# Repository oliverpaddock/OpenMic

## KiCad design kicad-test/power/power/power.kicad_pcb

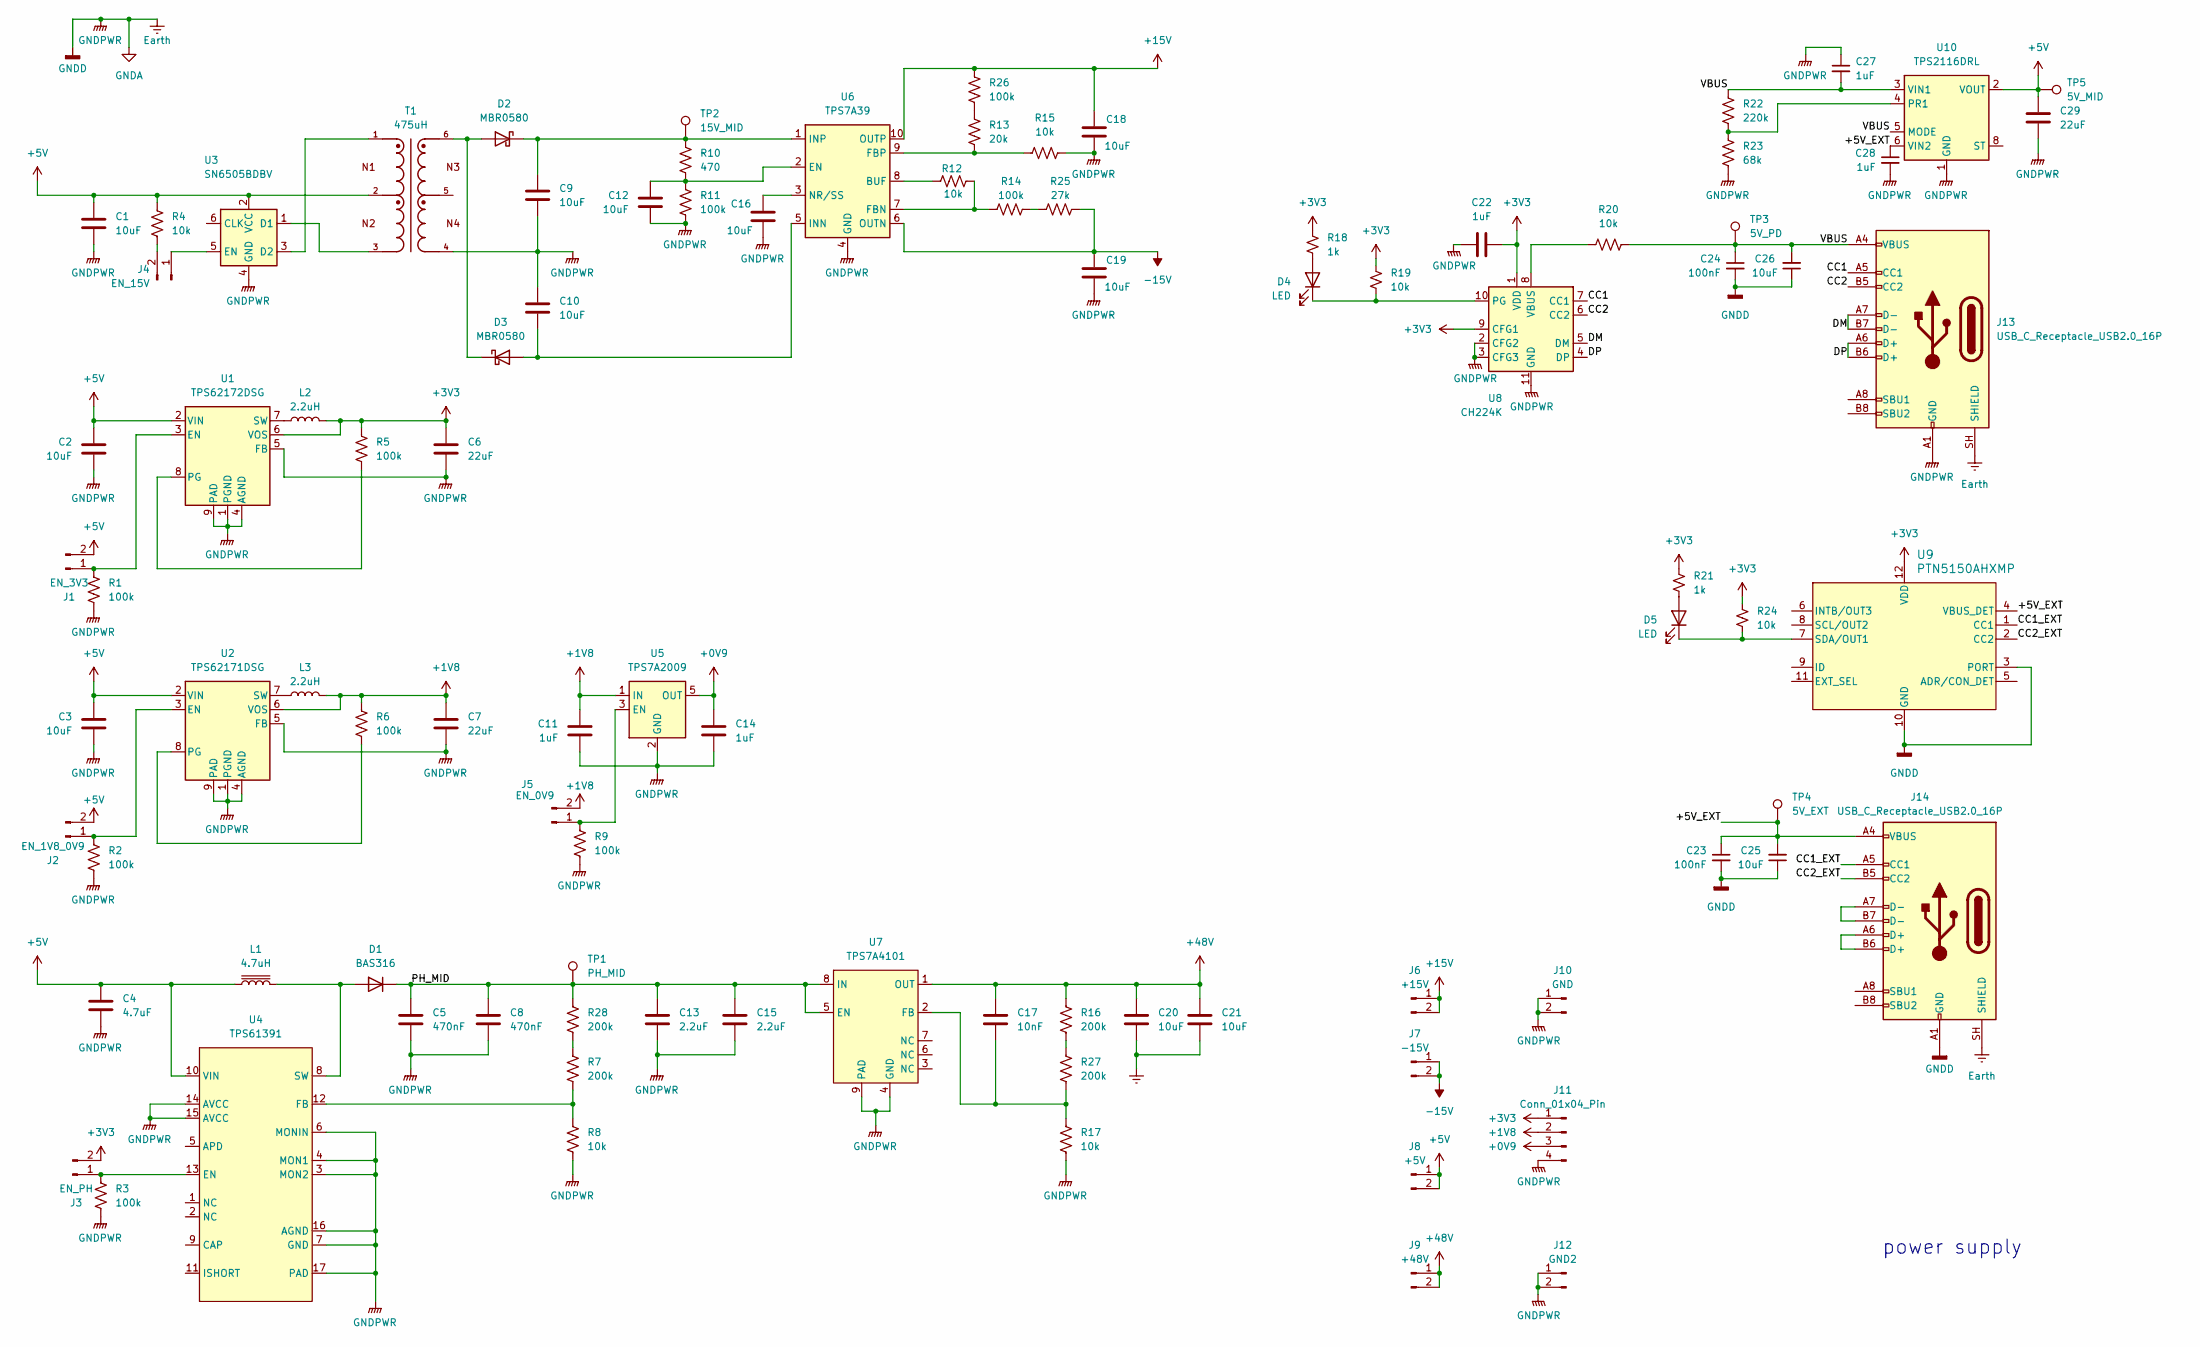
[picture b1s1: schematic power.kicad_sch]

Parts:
C1, C2, C3, C9, C10, C12, C16, C18, C19, C25, C26: 10uF; C_0805_2012Metric_Pad1.18x1.45mm_HandSolder; MPN CL21A106KAYNNNE; LCSC C15850
C4: 4.7uF; C_0805_2012Metric_Pad1.18x1.45mm_HandSolder; MPN CL21A475KAQNNNE; LCSC C1779
C5, C8: 470nF; C_0805_2012Metric_Pad1.18x1.45mm_HandSolder; MPN CL21B474KBFNNNE; LCSC C13967
C6, C7, C29: 22uF; C_0805_2012Metric_Pad1.18x1.45mm_HandSolder; MPN CL21A226MAQNNNE; LCSC C45783
C11, C14, C22, C27, C28: 1uF; C_0805_2012Metric_Pad1.18x1.45mm_HandSolder; MPN CL21B105KBFNNNE; LCSC C28323
C13, C15: 2.2uF; C_0805_2012Metric_Pad1.18x1.45mm_HandSolder; MPN CL21A225KBQNNNE; LCSC C377773
C17: 10nF; C_0805_2012Metric_Pad1.18x1.45mm_HandSolder; MPN CL21B103KBANNNC; LCSC C1710
C20, C21: 10uF; C_1210_3225Metric_Pad1.33x2.70mm_HandSolder; MPN CL21A106KAYNNNE; LCSC C15850
C23, C24: 100nF; C_0805_2012Metric_Pad1.18x1.45mm_HandSolder; MPN CC0805KRX7R9BB104; LCSC C49678
D1: BAS316; D_SOD-323; MPN BAS316; LCSC C8488
D2, D3: MBR0580; D_SOD-123; MPN MBR0580; LCSC C77339
D4, D5: LED; LED_0805_2012Metric_Pad1.15x1.40mm_HandSolder; MPN NCD0805R1; LCSC C84256
J1: EN_3V3; PinHeader_1x02_P2.54mm_Vertical
J2: EN_1V8_0V9; PinHeader_1x02_P2.54mm_Vertical
J3: EN_PH; PinHeader_1x02_P2.54mm_Vertical
J4: EN_15V; PinHeader_1x02_P2.54mm_Vertical
J5: EN_0V9; PinHeader_1x02_P2.54mm_Vertical
J6: +15V; PinHeader_1x02_P2.54mm_Vertical
J7: -15V; PinHeader_1x02_P2.54mm_Vertical
J8: +5V; PinHeader_1x02_P2.54mm_Vertical
J9: +48V; PinHeader_1x02_P2.54mm_Vertical
J10: GND; PinHeader_1x02_P2.54mm_Vertical
J11: Conn_01x04_Pin; PinHeader_1x04_P2.54mm_Vertical
J12: GND2; PinHeader_1x02_P2.54mm_Vertical
J13, J14: USB_C_Receptacle_USB2.0_16P; USB_C_Receptacle_HRO_TYPE-C-31-M-12; MPN TYPE-C-31-M-12; LCSC C165948
L1: 4.7uH; L_Wuerth_PMCI-201610; MPN DFE201612E-4R7M=P2; LCSC C3223763
L2, L3: 2.2uH; L_Wurth_WE-LQSH-3012; MPN ANR3015T2R2M; LCSC C6364793
R1, R2, R3, R5, R6, R9, R11, R14, R26: 100k; R_0805_2012Metric_Pad1.20x1.40mm_HandSolder; MPN 0805W8F1003T5E; LCSC C149504
R4, R8, R12, R15, R17, R19, R20, R24: 10k; R_0805_2012Metric_Pad1.20x1.40mm_HandSolder; MPN 0805W8F1002T5E; LCSC C17414
R7, R16, R27, R28: 200k; R_0805_2012Metric_Pad1.20x1.40mm_HandSolder; MPN 0805W8F2003T5E; LCSC C17539
R10: 470; R_0805_2012Metric_Pad1.20x1.40mm_HandSolder; MPN 0805W8F4700T5E; LCSC C17710
R13: 20k; R_0805_2012Metric_Pad1.20x1.40mm_HandSolder; MPN 0805W8F2002T5E; LCSC C4328
R18, R21: 1k; R_0805_2012Metric_Pad1.20x1.40mm_HandSolder; MPN 0805W8F1001T5E; LCSC C17513
R22: 220k; R_0805_2012Metric_Pad1.20x1.40mm_HandSolder; MPN 0805W8F2203T5E; LCSC C17556
R23: 68k; R_0805_2012Metric_Pad1.20x1.40mm_HandSolder; MPN 0805W8F6802T5E; LCSC C17801
R25: 27k; R_0805_2012Metric_Pad1.20x1.40mm_HandSolder; MPN 0805W8F2702T5E; LCSC C17593
T1: 475uH; Wurth Elektronik 760390015; MPN 760390015; LCSC C249186
TP1: PH_MID; TestPoint_Keystone_5010-5014_Multipurpose
TP2: 15V_MID; TestPoint_Keystone_5010-5014_Multipurpose
TP3: 5V_PD; TestPoint_Keystone_5010-5014_Multipurpose
TP4: 5V_EXT; TestPoint_Keystone_5010-5014_Multipurpose
TP5: 5V_MID; TestPoint_Keystone_5010-5014_Multipurpose
U1: TPS62172DSG; WSON-8-1EP_2x2mm_P0.5mm_EP0.9x1.6mm_ThermalVias; MPN TPS62172DSGR; LCSC C59873
U2: TPS62171DSG; WSON-8-1EP_2x2mm_P0.5mm_EP0.9x1.6mm_ThermalVias; MPN TPS62171DSGR; LCSC C2071102
U3: SN6505BDBV; SOT-23-6; MPN SN6505BDBVR; LCSC C74518
U4: TPS61391; WQFN-16-1EP_3x3mm_P0.5mm_EP1.6x1.6mm; MPN TPS61391RTER; LCSC C1852151
U5: TPS7A2009; SOT-23-5; MPN TPS7A2009PDBVR; LCSC C2861215
U6: TPS7A39; Texas_S-PVSON-N10_ThermalVias; MPN TPS7A3901DSCR; LCSC C2685819
U7: TPS7A4101; Texas_DGN0008B_VSSOP-8-1EP_3x3mm_P0.65mm_EP2x3mm_Mask1.88x1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; MPN TPS7A4101DGNR; LCSC C111739
U8: CH224K; SSOP-10-1EP_3.9x4.9mm_P1mm_EP2.1x3.3mm; MPN CH224K; LCSC C970725
U9: PTN5150AHXMP; Texas_X2QFN-12_1.6x1.6mm_P0.4mm; MPN PTN5150AHXMP; LCSC C2651889
U10: TPS2116DRL; SOT-583-8; MPN TPS2116DRLR; LCSC C3235557

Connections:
+0V9: C14.1, J11.3, U5.5 (OUT)
+1V8: C7.1, C11.1, J5.2, J11.2, L3.2, R6.1, U2.6 (VOS), U5.1 (IN)
+3V3: C6.1, C22.1, J3.2, J11.1, L2.2, R5.1, R18.1, R19.1, R21.1, R24.1, U1.6 (VOS), U8.1 (VDD), U8.9 (CFG1), U9.12 (VDD)
+5V: C1.1, C2.1, C3.1, C4.1, C29.1, J1.2, J2.2, J8.1, J8.2, L1.1, R4.2, T1.2, TP5.1 (1_1), U1.2 (VIN), U2.2 (VIN), U3.2 (VCC), U4.10 (VIN), U10.2 (VOUT), U10.7 (VOUT)
+15V: C18.1, J6.1, J6.2, R26.1, U6.10 (OUTP)
+48V: C17.1, C20.1, C21.1, J9.1, J9.2, R16.1, U7.1 (OUT)
-15V: C19.1, J7.1, J7.2, R25.2, U6.6 (OUTN)
/+5V_EXT: C23.1, C25.2, C28.1, J14.A4 (VBUS), J14.A9 (VBUS), J14.B4 (VBUS), J14.B9 (VBUS), TP4.1 (1_1), U9.4 (VBUS_DET), U10.6 (VIN2)
/CC1: J13.A5 (CC1), U8.7 (CC1)
/CC1_EXT: J14.A5 (CC1), U9.1 (CC1)
/CC2: J13.B5 (CC2), U8.6 (CC2)
/CC2_EXT: J14.B5 (CC2), U9.2 (CC2)
/DM: J13.A7 (D-), J13.B7 (D-), U8.5 (DM)
/DP: J13.A6 (D+), J13.B6 (D+), U8.4 (DP)
/PH_MID: C5.1, C8.1, C13.1, C15.1, D1.1 (K), R28.1, TP1.1 (1_1), U7.5 (EN), U7.8 (IN)
/VBUS: C24.1, C26.2, C27.2, J13.A4 (VBUS), J13.A9 (VBUS), J13.B4 (VBUS), J13.B9 (VBUS), R20.2, R22.1, TP3.1 (1_1), U10.3 (VIN1), U10.5 (MODE)
Earth: C1.2, C2.2, C3.2, C4.2, C5.2, C6.2, C7.2, C8.2, C9.2, C10.1, C11.2, C12.2, C13.2, C14.2, C15.2, C16.2, C18.2, C19.2, C20.2, C21.2, C22.2, C23.2, C24.2, C25.1, C26.1, C27.1, C28.2, C29.2, J10.1, J10.2, J11.4, J12.1, J12.2, J13.A1 (GND), J13.A12 (GND), J13.B1 (GND), J13.B12 (GND), J13.SH (SHIELD), J14.A1 (GND), J14.A12 (GND), J14.B1 (GND), J14.B12 (GND), J14.SH (SHIELD), R1.2, R2.2, R3.2, R8.2, R9.2, R11.2, R15.2, R17.2, R23.2, T1.4, U1.1 (PGND), U1.4 (AGND), U1.5 (FB), U1.9 (PAD), U2.1 (PGND), U2.4 (AGND), U2.5 (FB), U2.9 (PAD), U3.4 (GND), U4.3 (MON2), U4.4 (MON1), U4.6 (MONIN), U4.7 (GND), U4.14 (AVCC), U4.15 (AVCC), U4.16 (AGND), U4.17 (PAD), U5.2 (GND), U6.4 (GND), U6.11 (GND), U7.4 (GND), U7.9 (PAD), U8.2 (CFG2), U8.3 (CFG3), U8.11 (GND), U9.3 (PORT), U9.10 (GND), U10.1 (GND)
unnamed: D1.2 (A), L1.2, U4.8 (SW)
unnamed: D2.2 (A), D3.1 (K), T1.6
unnamed: C9.1, D2.1 (K), R10.1, TP2.1 (1_1), U6.1 (INP)
unnamed: C10.2, D3.2 (A), U6.5 (INN)
unnamed: D4.2 (A), R18.2
unnamed: D4.1 (K), R19.2, U8.10 (PG)
unnamed: D5.2 (A), R21.2
unnamed: D5.1 (K), R24.2, U9.7 (SDA/OUT1)
unnamed: J1.1, R1.1, U1.3 (EN)
unnamed: J2.1, R2.1, U2.3 (EN)
unnamed: J3.1, R3.1, U4.13 (EN)
unnamed: J4.1, U3.5 (EN)
unnamed: J4.2, R4.1
unnamed: J5.1, R9.1, U5.3 (EN)
unnamed: J14.A6 (D+), J14.B6 (D+)
unnamed: J14.A7 (D-), J14.B7 (D-)
unnamed: R13.1, R26.2
unnamed: R14.2, R25.1
unnamed: R16.2, R27.1
unnamed: R7.1, R28.2
unnamed: R5.2, U1.8 (PG)
unnamed: L2.1, U1.7 (SW)
unnamed: R6.2, U2.8 (PG)
unnamed: L3.1, U2.7 (SW)
unnamed: T1.3, U3.1 (D1)
unnamed: T1.1, U3.3 (D2)
unnamed: R7.2, R8.1, U4.12 (FB)
unnamed: R12.1, U6.8 (BUF)
unnamed: C12.1, R10.2, R11.1, U6.2 (EN)
unnamed: R12.2, R14.1, U6.7 (FBN)
unnamed: R13.2, R15.1, U6.9 (FBP)
unnamed: C16.1, U6.3 (NR/SS)
unnamed: C17.2, R17.1, R27.2, U7.2 (FB)
unnamed: R20.1, U8.8 (VBUS)
unnamed: R22.2, R23.1, U10.4 (PR1)

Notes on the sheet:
power supply

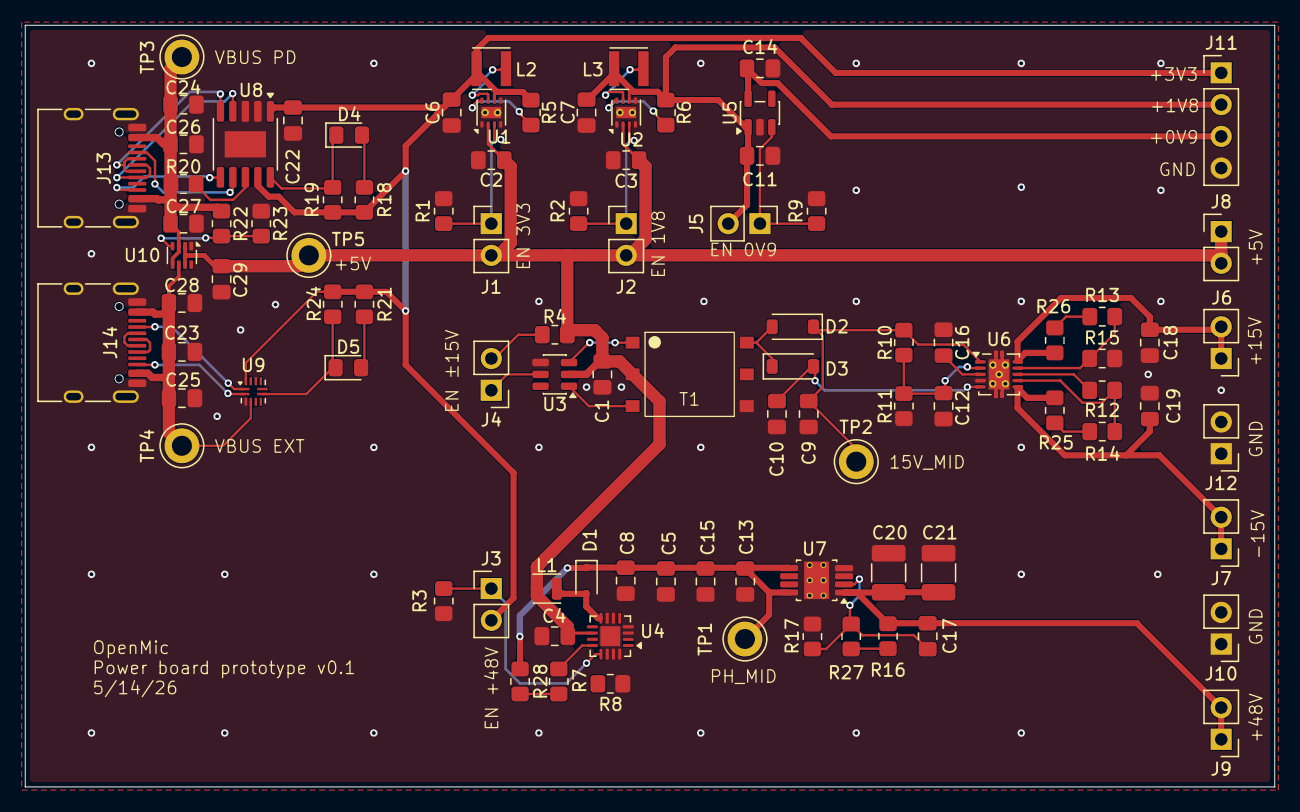
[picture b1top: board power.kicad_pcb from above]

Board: 2 copper layers, 100.0 x 61.0 mm, 95 parts (0 on the bottom side), 52 nets.

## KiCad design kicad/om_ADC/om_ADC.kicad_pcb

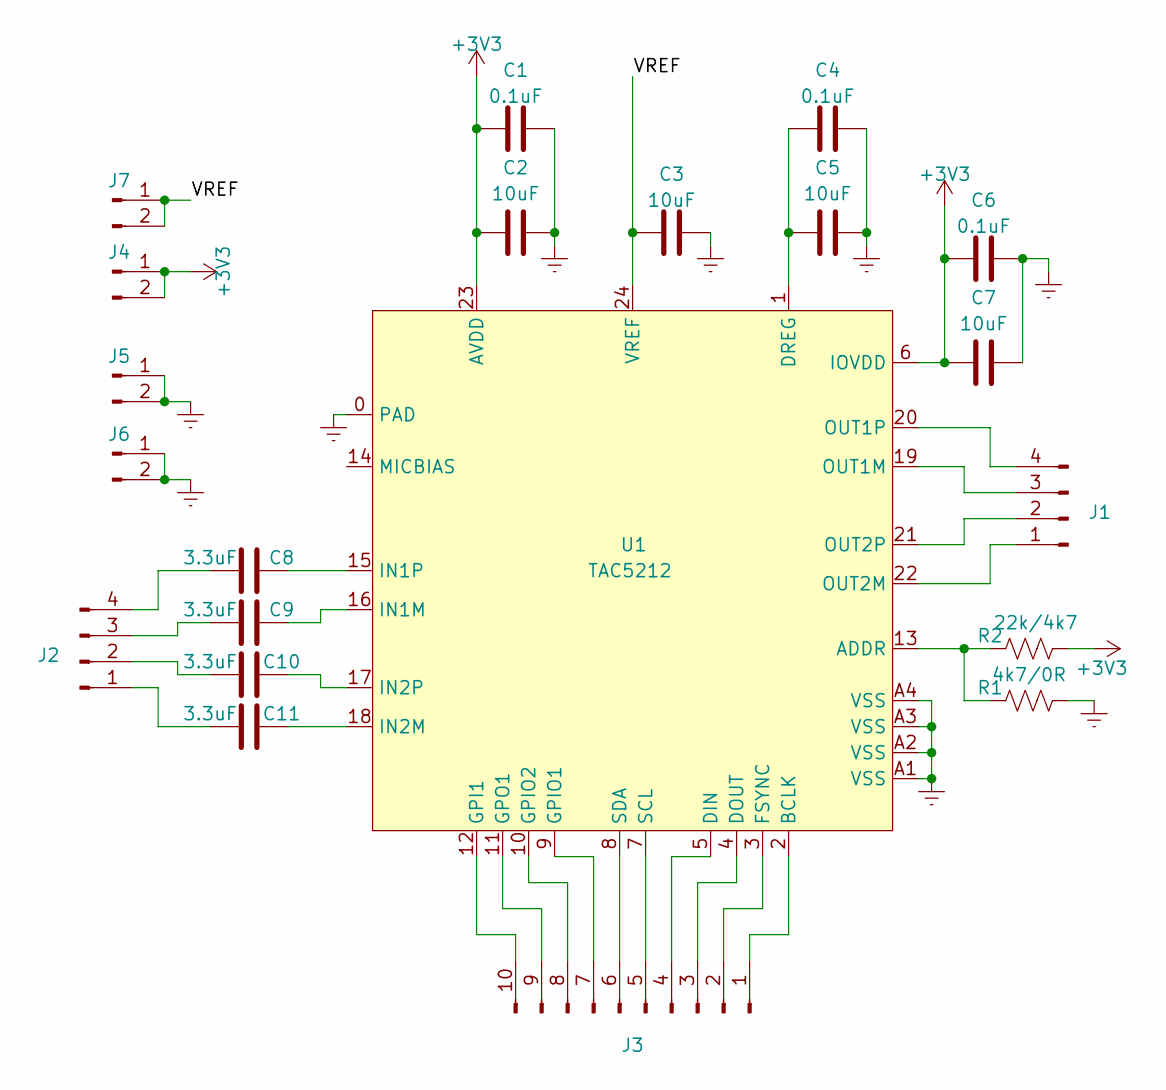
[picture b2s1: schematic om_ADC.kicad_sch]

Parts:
C1, C4, C6: 0.1uF; C_0603_1608Metric_Pad1.08x0.95mm_HandSolder
C2, C3, C5, C7: 10uF; C_0603_1608Metric_Pad1.08x0.95mm_HandSolder
C8, C9, C10, C11: 3.3uF; C_0603_1608Metric_Pad1.08x0.95mm_HandSolder
J1, J2: Conn_01x04_Pin; PinHeader_1x04_P2.54mm_Vertical
J3: Conn_01x10_Pin; PinHeader_1x10_P2.54mm_Vertical
J4, J5, J6, J7: Conn_01x02_Pin; PinHeader_1x02_P2.54mm_Vertical
R1: 4k7/0R; R_0603_1608Metric_Pad0.98x0.95mm_HandSolder
R2: 22k/4k7; R_0603_1608Metric_Pad0.98x0.95mm_HandSolder
U1: TAC5212

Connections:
+3V3: C1.1, C2.1, C6.1, C7.1, J4.1, J4.2, R2.2, U1.6 (IOVDD), U1.23 (AVDD)
/VREF: C3.1, J7.1, J7.2, U1.24 (VREF)
Earth: C1.2, C2.2, C3.2, C4.2, C5.2, C6.2, C7.2, J5.1, J5.2, J6.1, J6.2, R1.2, U1.0 (PAD), U1.A1 (VSS), U1.A2 (VSS), U1.A3 (VSS), U1.A4 (VSS)
unnamed: J1.1, U1.22 (OUT2M)
unnamed: J1.2, U1.21 (OUT2P)
unnamed: J1.3, U1.19 (OUT1M)
unnamed: J1.4, U1.20 (OUT1P)
unnamed: C11.1, J2.1
unnamed: C10.1, J2.2
unnamed: C9.1, J2.3
unnamed: C8.1, J2.4
unnamed: J3.1, U1.2 (BCLK)
unnamed: J3.2, U1.3 (FSYNC)
unnamed: J3.3, U1.4 (DOUT)
unnamed: J3.4, U1.5 (DIN)
unnamed: J3.5, U1.7 (SCL)
unnamed: J3.6, U1.8 (SDA)
unnamed: J3.7, U1.9 (GPIO1)
unnamed: J3.8, U1.10 (GPIO2)
unnamed: J3.9, U1.11 (GPO1)
unnamed: J3.10, U1.12 (GPI1)
unnamed: R1.1, R2.1, U1.13 (ADDR)
unnamed: C4.1, C5.1, U1.1 (DREG)
unnamed: C9.2, U1.16 (IN1M)
unnamed: C8.2, U1.15 (IN1P)
unnamed: C11.2, U1.18 (IN2M)
unnamed: C10.2, U1.17 (IN2P)

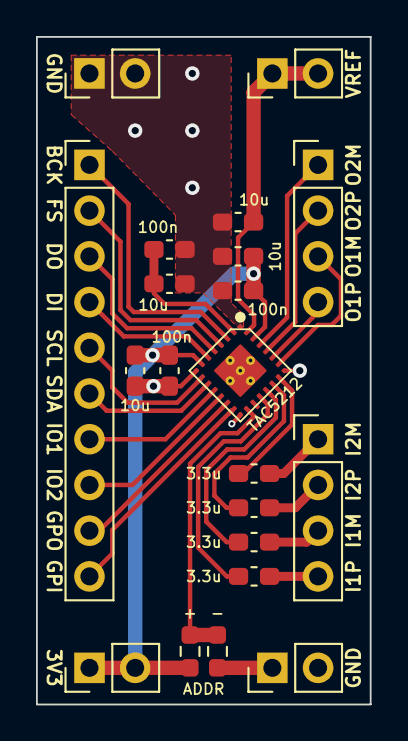
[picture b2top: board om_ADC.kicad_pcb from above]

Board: 2 copper layers, 18.5 x 37.1 mm, 21 parts (0 on the bottom side), 27 nets.

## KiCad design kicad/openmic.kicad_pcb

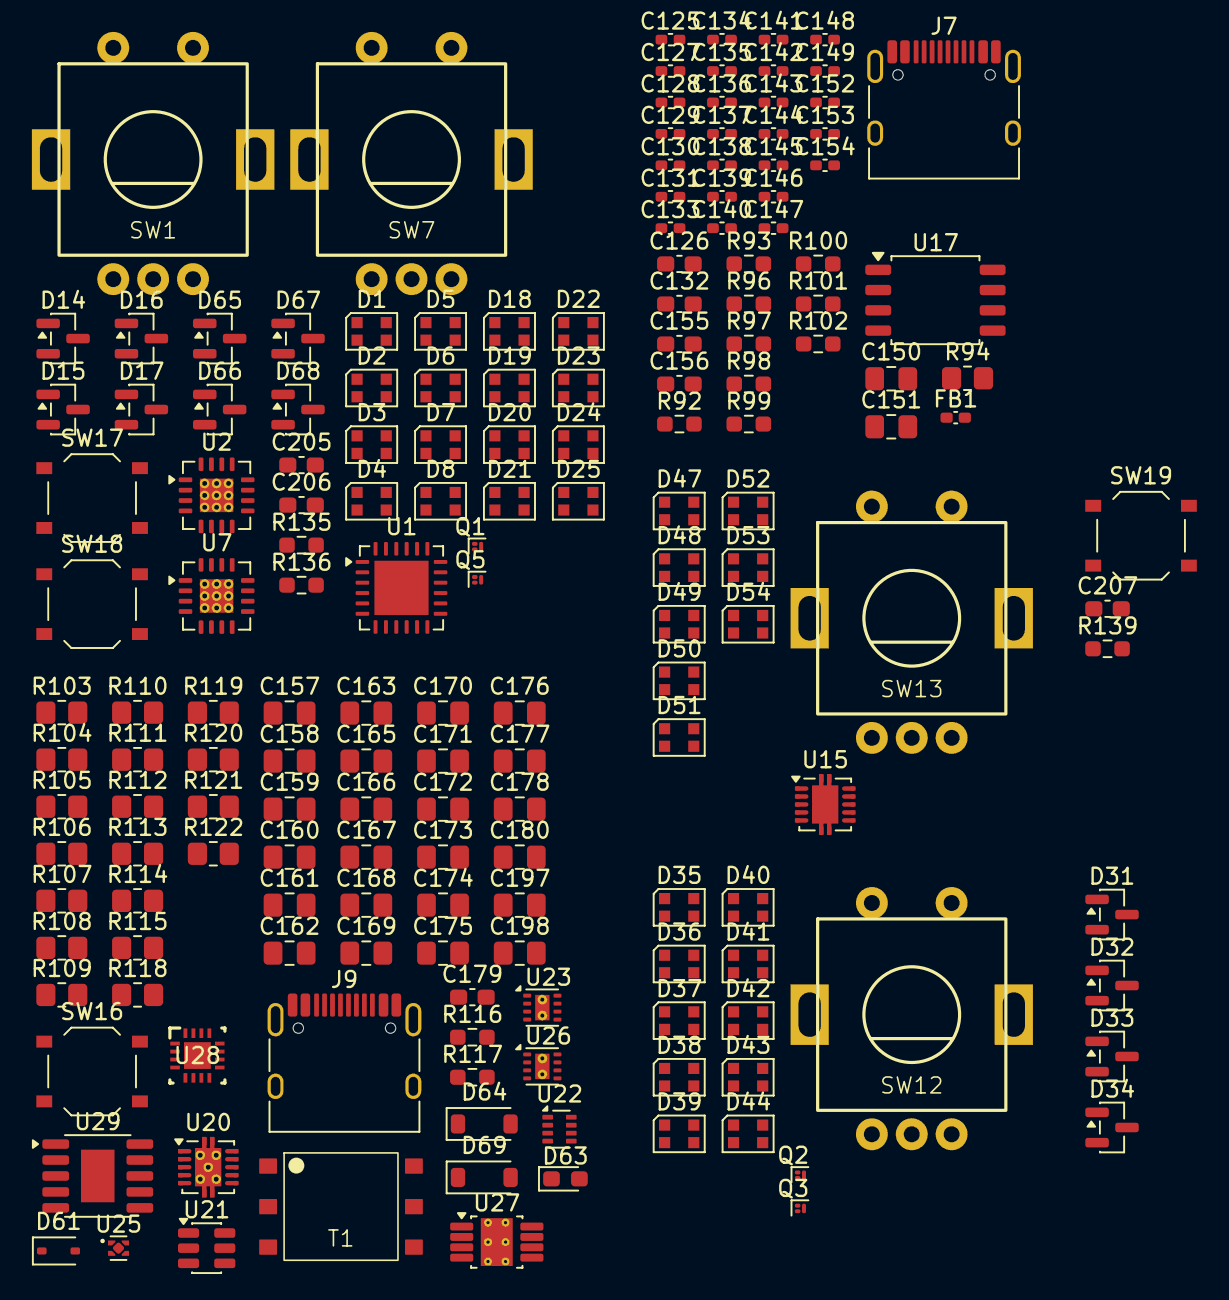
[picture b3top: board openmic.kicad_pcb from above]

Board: 2 copper layers, 173 parts (0 on the bottom side), 98 nets, no tracks yet.

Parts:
C125, C127, C128, C129, C130, C131, C133, C134, C135, C136, C137, C138, C139, C140, C141, C142, C143, C144, C145, C146, C147, C148, C149, C153, C154: 100nF; C_0402_1005Metric_Pad0.74x0.62mm_HandSolder
C126, C132, C179, C205, C206, C207: 100nF; C_0603_1608Metric_Pad1.08x0.95mm_HandSolder
C150, C197: 100nF; C_0805_2012Metric_Pad1.18x1.45mm_HandSolder
C151, C157, C158, C159, C160, C161, C162, C165, C167, C177, C178, C198: 10uF; C_0805_2012Metric_Pad1.18x1.45mm_HandSolder
C152: 1uF; C_0402_1005Metric_Pad0.74x0.62mm_HandSolder
C155, C156: 22pF; C_0603_1608Metric_Pad1.08x0.95mm_HandSolder
C163, C166, C168: 22uF; C_0805_2012Metric_Pad1.18x1.45mm_HandSolder
C169, C170, C180: 1uF; C_0805_2012Metric_Pad1.18x1.45mm_HandSolder
C171: 4.7uF; C_0805_2012Metric_Pad1.18x1.45mm_HandSolder
C172, C173: 470nF; C_0805_2012Metric_Pad1.18x1.45mm_HandSolder
C174, C175: 2.2uF; C_0805_2012Metric_Pad1.18x1.45mm_HandSolder
C176: 10nF; C_0805_2012Metric_Pad1.18x1.45mm_HandSolder
D1, D2, D3, D4, D5, D6, D7, D8, D18, D19, D20, D21, D22, D23, D24, D25, D35, D36, D37, D38, D39, D40, D41, D42, D43, D44, D47, D48, D49, D50, D51, D52, D53, D54: WS2812B-2020; LED_WS2812B-2020_PLCC4_2.0x2.0mm
D14, D15, D16, D17, D65, D66, D67, D68: BAV99; SOT-23
D31, D32, D33, D34: BAT54S; SOT-23
D61: BAS316; D_SOD-323
D63: LED; LED_0603_1608Metric_Pad1.05x0.95mm_HandSolder
D64, D69: MBR0580; D_SOD-123
FB1: 600R; L_0402_1005Metric_Pad0.77x0.64mm_HandSolder
J7, J9: USB_C_Receptacle_USB2.0_16P; USB_C_Receptacle_HRO_TYPE-C-31-M-12
Q1, Q2, Q3, Q5: CSD13380F3; Texas_PicoStar_DFN-3_0.69x0.60mm
R92, R96, R98, R99, R100, R116, R135, R136, R139: 47k; R_0603_1608Metric_Pad0.98x0.95mm_HandSolder
R93: 220k; R_0603_1608Metric_Pad0.98x0.95mm_HandSolder
R94, R104, R106, R108, R113, R120, R122: 10k; R_0805_2012Metric_Pad1.20x1.40mm_HandSolder
R97: 100k; R_0603_1608Metric_Pad0.98x0.95mm_HandSolder
R101: 1M; R_0603_1608Metric_Pad0.98x0.95mm_HandSolder
R102: 30; R_0603_1608Metric_Pad0.98x0.95mm_HandSolder
R103: 118k; R_0805_2012Metric_Pad1.20x1.40mm_HandSolder
R105: 499k; R_0805_2012Metric_Pad1.20x1.40mm_HandSolder
R107, R111, R112, R114: 100k; R_0805_2012Metric_Pad1.20x1.40mm_HandSolder
R109: 127k; R_0805_2012Metric_Pad1.20x1.40mm_HandSolder
R110: 330k; R_0805_2012Metric_Pad1.20x1.40mm_HandSolder
R115: 475k; R_0805_2012Metric_Pad1.20x1.40mm_HandSolder
R117: 1k; R_0603_1608Metric_Pad0.98x0.95mm_HandSolder
R118: 392k; R_0805_2012Metric_Pad1.20x1.40mm_HandSolder
R119: 12k; R_0805_2012Metric_Pad1.20x1.40mm_HandSolder
R121: 1k; R_0805_2012Metric_Pad1.20x1.40mm_HandSolder
SW1, SW7, SW12, SW13: RotaryEncoder; PEC11L
SW16, SW17, SW18, SW19: SW_Push; SW_Push_1P1T_XKB_TS-1187A
T1: 475uH; Wurth Elektronik 760390015
U1: THAT5263; QFN-24-1EP_5x5mm_P0.65mm_EP3.4x3.4mm
U2, U7: THAT1580; QFN-16-1EP_4x4mm_P0.65mm_EP2.1x2.1mm_ThermalVias
U15: OPA1622; Texas_S-PVSON-N10
U17: W25Q32JVSS; SOIC-8_5.3x5.3mm_P1.27mm
U20: TPS7A39; Texas_S-PVSON-N10_ThermalVias
U21: SN6505BDBV; SOT-23-6
U22: TPS2116DRL; SOT-583-8
U23: TPS62172DSG; WSON-8-1EP_2x2mm_P0.5mm_EP0.9x1.6mm_ThermalVias
U25: TPS7A2009; Texas_X2SON-4_1x1mm_P0.65mm
U26: TPS62171DSG; WSON-8-1EP_2x2mm_P0.5mm_EP0.9x1.6mm_ThermalVias
U27: TPS7A4101; Texas_DGN0008B_VSSOP-8-1EP_3x3mm_P0.65mm_EP2x3mm_Mask1.88x1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
U28: TPS61391
U29: CH224K; SSOP-10-1EP_3.9x4.9mm_P1mm_EP2.1x3.3mm

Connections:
+0V9: C125.1, C127.1, C128.1, C129.1, C130.1, C131.1, C133.1, C134.1, C135.1, C136.1, C137.1, C138.1, C139.1, C140.1, C141.1, C170.1, FB1.2, U25.1 (OUT)
+1V8: C126.1, C148.1, C149.1, C153.1, C168.1, C169.1, R114.1, U25.3 (EN), U25.4 (IN), U26.6 (VOS)
+3V3: C132.1, C142.1, C143.1, C144.1, C145.1, C146.1, C147.1, C154.1, C166.1, D31.2 (K), D32.2 (K), D33.2 (K), D34.2 (K), R92.1, R94.1, R98.1, R99.1, R100.1, R112.1, R113.1, R116.1, R135.1, R136.1, R139.1, U1.15 (VDD), U17.8 (VCC), U23.6 (VOS)
+5V: C161.1, C163.1, C165.1, C167.1, C171.1, D1.4 (VDD), D2.4 (VDD), D3.4 (VDD), D4.4 (VDD), D5.4 (VDD), D6.4 (VDD), D7.4 (VDD), D8.4 (VDD), D18.4 (VDD), D19.4 (VDD), D20.4 (VDD), D21.4 (VDD), D22.4 (VDD), D23.4 (VDD), D24.4 (VDD), D25.4 (VDD), D35.4 (VDD), D36.4 (VDD), D37.4 (VDD), D38.4 (VDD), D39.4 (VDD), D40.4 (VDD), D41.4 (VDD), D42.4 (VDD), D43.4 (VDD), D44.4 (VDD), D47.4 (VDD), D48.4 (VDD), D49.4 (VDD), D50.4 (VDD), D51.4 (VDD), D52.4 (VDD), D53.4 (VDD), D54.4 (VDD), R108.2, T1.2, U21.2 (VCC), U22.2 (VOUT), U22.7 (VOUT), U23.2 (VIN), U23.3 (EN), U26.2 (VIN), U26.3 (EN), U28.10 (VIN)
+15V: C157.1, D14.2 (A), D15.2 (A), D16.2 (A), D17.2 (A), D65.2 (A), D66.2 (A), D67.2 (A), D68.2 (A), R103.1, U1.4 (V+), U2.13 (V+), U7.13 (V+), U15.2 (V+), U20.10 (OUTP)
-15V: D14.1 (K), D15.1 (K), D16.1 (K), D17.1 (K), D65.1 (K), D66.1 (K), D67.1 (K), D68.1 (K), R106.2, R109.1, R109.2, U1.3 (V-), U1.25 (PAD), U2.12 (V-), U2.17 (V-), U7.12 (V-), U7.17 (V-), U15.4 (V-), U15.11 (V-), U20.6 (OUTN), U20.7 (FBN)
/input/+48V_PH: C176.1, C177.1, C178.1, R115.1, U27.1 (OUT)
/input/INST_IND_1: C205.1, R135.2, SW17.1
/input/INST_IND_2: C206.1, R136.2, SW18.1
/input/IN_EN_1: Q5.1 (G), U1.19 (GPO_CH1)
/input/IN_EN_2: Q1.1 (G), U1.20 (GPO_CH2)
/input/LED_1_DOUT: D8.1 (DOUT), D18.3 (DIN)
/input/LED_2_DOUT: D25.1 (DOUT), D47.3 (DIN)
/input/MIC_1_N: U1.10 (IN2_CH1), U2.2
/input/MIC_1_P: U1.5 (IN1_CH1), U2.3 (1)
/input/MIC_2_N: U1.2 (IN2_CH2), U7.2
/input/MIC_2_P: U1.21 (IN1_CH2), U7.3 (1)
/line driver/LED_DIN: D35.3 (DIN), D54.1 (DOUT)
/power supply/CC1: J9.A5 (CC1), U29.7 (CC1)
/power supply/CC2: J9.B5 (CC2), U29.6 (CC2)
/power supply/CH224K_VDD: C180.1, R121.2, U29.1 (VDD), U29.9 (CFG1)
/power supply/DM: J9.A7 (D-), J9.B7 (D-), U29.5 (DM)
/power supply/DP: J9.A6 (D+), J9.B6 (D+), U29.4 (DP)
/power supply/VBUS: C197.1, C198.2, J9.A4 (VBUS), J9.A9 (VBUS), J9.B4 (VBUS), J9.B9 (VBUS), R110.1, R122.2, U22.3 (VIN1), U22.5 (MODE)
/usb bridge/GP0_8C_0: R98.2, U1.11 (~CS)
/usb bridge/GP0_8C_3: R117.1, U28.13 (EN)
/usb bridge/GP0_8D_1: R113.2, U29.10 (PG)
/usb bridge/GP0_8D_3: C179.1, R116.2, SW16.1
/usb bridge/GP0_8D_7: C207.1, R139.2, SW19.1
/usb bridge/IOB_GP0_1E: R93.2, R97.1
/usb bridge/PLL_AVDD: C152.1, FB1.1
/usb bridge/QSPI_CS: R92.2, U17.1 (~CS)
/usb bridge/VBUS: C150.1, C151.2, J7.A4 (VBUS), J7.A9 (VBUS), J7.B4 (VBUS), J7.B9 (VBUS), R93.1, R96.1, U22.6 (VIN2)
Earth: C125.2, C126.2, C127.2, C128.2, C129.2, C130.2, C131.2, C132.2, C133.2, C134.2, C135.2, C136.2, C137.2, C138.2, C139.2, C140.2, C141.2, C142.2, C143.2, C144.2, C145.2, C146.2, C147.2, C148.2, C149.2, C150.2, C151.1, C152.2, C153.2, C154.2, C155.1, C156.1, C157.2, C158.2, C159.2, C160.2, C161.2, C162.1, C163.2, C165.2, C166.2, C167.2, C168.2, C169.2, C170.2, C171.2, C172.2, C173.2, C174.2, C175.2, C177.2, C178.2, C179.2, C180.2, C197.2, C198.1, C205.2, C206.2, C207.2, D1.2 (VSS), D2.2 (VSS), D3.2 (VSS), D4.2 (VSS), D5.2 (VSS), D6.2 (VSS), D7.2 (VSS), D8.2 (VSS), D18.2 (VSS), D19.2 (VSS), D20.2 (VSS), D21.2 (VSS), D22.2 (VSS), D23.2 (VSS), D24.2 (VSS), D25.2 (VSS), D31.1 (A), D32.1 (A), D33.1 (A), D34.1 (A), D35.2 (VSS), D36.2 (VSS), D37.2 (VSS), D38.2 (VSS), D39.2 (VSS), D40.2 (VSS), D41.2 (VSS), D42.2 (VSS), D43.2 (VSS), D44.2 (VSS), D47.2 (VSS), D48.2 (VSS), D49.2 (VSS), D50.2 (VSS), D51.2 (VSS), D52.2 (VSS), D53.2 (VSS), D54.2 (VSS), D63.1 (K), J7.A1 (GND), J7.A12 (GND), J7.B1 (GND), J7.B12 (GND), J9.A1 (GND), J9.A12 (GND), J9.B1 (GND), J9.B12 (GND), Q1.2 (S), Q2.2 (S), Q3.2 (S), Q5.2 (S), R96.2, R97.2, R104.2, R107.2, R111.2, R119.2, R120.2, SW1.C, SW7.C, SW12.C, SW13.C, SW16.2, SW17.2, SW18.2, SW19.2, T1.4, U1.16 (DGND), U15.3 (GND), U17.4 (GND), U20.4 (GND), U20.11 (GND), U21.4 (GND), U22.1 (GND), U23.1 (PGND), U23.4 (AGND), U23.5 (FB), U23.9 (PAD), U25.2 (GND), U25.5 (Pad), U26.1 (PGND), U26.4 (AGND), U26.5 (FB), U26.9 (PAD), U27.4 (GND), U28.3 (MON2), U28.4 (MON1), U28.6 (MONIN), U28.7 (GND), U28.14 (AVCC), U28.15 (AVCC), U28.16 (AGND), U29.11 (GND)
unnamed: C155.2, R102.1
unnamed: D1.1 (DOUT), D2.3 (DIN)
unnamed: D2.1 (DOUT), D3.3 (DIN)
unnamed: D3.1 (DOUT), D4.3 (DIN)
unnamed: D4.1 (DOUT), D5.3 (DIN)
unnamed: D5.1 (DOUT), D6.3 (DIN)
unnamed: D6.1 (DOUT), D7.3 (DIN)
unnamed: D7.1 (DOUT), D8.3 (DIN)
unnamed: D18.1 (DOUT), D19.3 (DIN)
unnamed: D19.1 (DOUT), D20.3 (DIN)
unnamed: D20.1 (DOUT), D21.3 (DIN)
unnamed: D21.1 (DOUT), D22.3 (DIN)
unnamed: D22.1 (DOUT), D23.3 (DIN)
unnamed: D23.1 (DOUT), D24.3 (DIN)
unnamed: D24.1 (DOUT), D25.3 (DIN)
unnamed: D35.1 (DOUT), D36.3 (DIN)
unnamed: D36.1 (DOUT), D37.3 (DIN)
unnamed: D37.1 (DOUT), D38.3 (DIN)
unnamed: D38.1 (DOUT), D39.3 (DIN)
unnamed: D39.1 (DOUT), D40.3 (DIN)
unnamed: D40.1 (DOUT), D41.3 (DIN)
unnamed: D41.1 (DOUT), D42.3 (DIN)
unnamed: D42.1 (DOUT), D43.3 (DIN)
unnamed: D43.1 (DOUT), D44.3 (DIN)
unnamed: D47.1 (DOUT), D48.3 (DIN)
unnamed: D48.1 (DOUT), D49.3 (DIN)
unnamed: D49.1 (DOUT), D50.3 (DIN)
unnamed: D50.1 (DOUT), D51.3 (DIN)
unnamed: D51.1 (DOUT), D52.3 (DIN)
unnamed: D52.1 (DOUT), D53.3 (DIN)
unnamed: D53.1 (DOUT), D54.3 (DIN)
unnamed: D61.2 (A), U28.8 (SW)
unnamed: C172.1, C173.1, C174.1, C175.1, D61.1 (K), R118.1, U27.5 (EN), U27.8 (IN)
unnamed: D63.2 (A), R117.2
unnamed: D64.2 (A), D69.1 (K), T1.6
unnamed: C158.1, D64.1 (K), R105.1, U20.1 (INP)
unnamed: C162.2, D69.2 (A), U20.5 (INN)
unnamed: U1.6 (RA_CH1), U2.6 (Rg1)
unnamed: U1.8 (RG2_CH1), U1.9 (RB_CH1), U2.15 (Rg2)
unnamed: U1.22 (RA_CH2), U7.6 (Rg1)
unnamed: U1.1 (RB_CH2), U1.24 (RG2_CH2), U7.15 (Rg2)
unnamed: D14.3 (K), U2.7 (IN1)
unnamed: D15.3 (K), U2.10 (IN2)
unnamed: D16.3 (K), U7.7 (IN1)
unnamed: D17.3 (K), U7.10 (IN2)
unnamed: U15.9, U15.10 (-)
unnamed: U15.6 (-), U15.7
unnamed: C156.2, R101.2
unnamed: R101.1, R102.2
unnamed: J7.A7 (D-), J7.B7 (D-)
unnamed: J7.A6 (D+), J7.B6 (D+)
unnamed: R106.1, U20.8 (BUF)
unnamed: C159.1, R105.2, R107.1, U20.2 (EN)
unnamed: R103.2, R104.1, U20.9 (FBP)
unnamed: C160.1, U20.3 (NR/SS)
unnamed: T1.3, U21.1 (D1)
unnamed: T1.1, U21.3 (D2)
unnamed: R108.1, U21.5 (EN)
unnamed: R110.2, R111.1, U22.4 (PR1)
unnamed: R112.2, U23.8 (PG)
unnamed: R114.2, U26.8 (PG)
unnamed: C176.2, R115.2, R119.1, U27.2 (FB)
unnamed: R118.2, R120.1, U28.12 (FB)
unnamed: R121.1, R122.1, U29.8 (VBUS)
